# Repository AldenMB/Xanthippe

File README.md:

# Xanthippe

This is the validation back-end for my TI-30Xa emulator. It is constantly pressing buttons on a TI-30Xa calculator and recording what the LCD shows. The results get stored in an SQLite database. The database is too big to be stored on github, but you can download a CSV from [https://home.aldenbradford.com:58086/](https://home.aldenbradford.com:58086/). In addition, whenever anyone uses the calculator at [https://aldenbradford.com/calculator_emulator/](https://aldenbradford.com/calculator_emulator/) the sequence of button presses is sent to Xanthippe to be tested. It will show up in the database the following day.

For more information about this project, [please see my blog](https://aldenbradford.com/tag/xanthippe.html).

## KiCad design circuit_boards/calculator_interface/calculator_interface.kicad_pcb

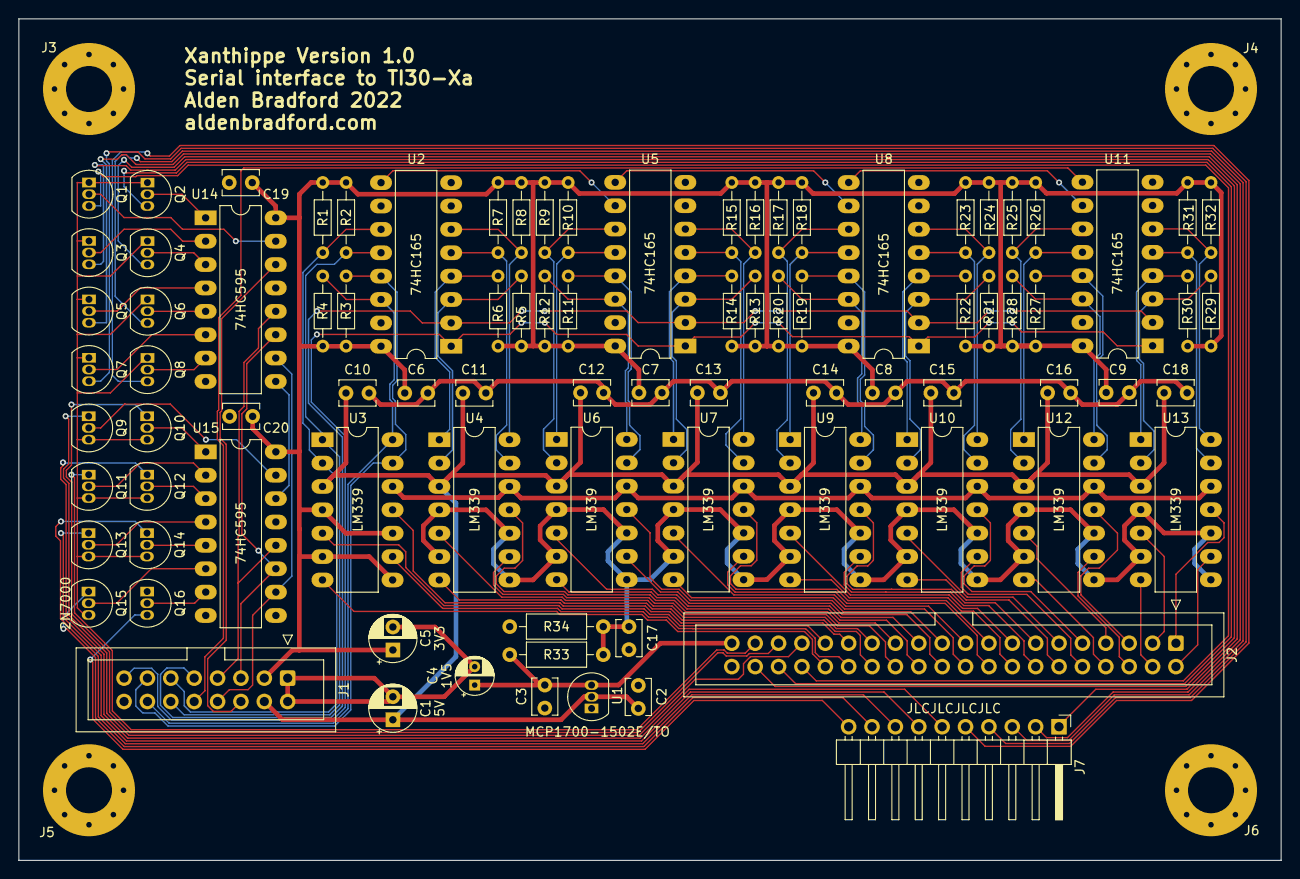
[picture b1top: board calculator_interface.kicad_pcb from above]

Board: 2 copper layers, 137.2 x 91.4 mm, 92 parts (0 on the bottom side), 113 nets.

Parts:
C1, C5: 100uF; CP_Radial_D5.0mm_P2.50mm
C2, C3, C6, C7, C8, C9, C10, C11, C12, C13, C14, C15, C16, C17, C18, C19, C20: 0.1uF; C_Disc_D3.8mm_W2.6mm_P2.50mm
C4: 10uF; CP_Radial_D4.0mm_P2.00mm
J1: Conn_02x08_Interface_Side; IDC-Header_2x08_P2.54mm_Vertical
J2: Conn_02x20_TI30XA; IDC-Header_2x20_P2.54mm_Vertical
J3, J4, J5, J6: Conn_01x01; MountingHole_5mm_Pad_Via
J7: Conn_01x10_TI30XA; PinHeader_1x10_P2.54mm_Horizontal
Q1, Q2, Q3, Q4, Q5, Q6, Q7, Q8, Q9, Q10, Q11, Q12, Q13, Q14, Q15, Q16: 2N7000; TO-92_Inline
R1, R2, R3, R4, R5, R6, R7, R8, R9, R10, R11, R12, R13, R14, R15, R16, R17, R18, R19, R20, R21, R22, R23, R24, R25, R26, R27, R28, R29, R30, R31, R32: 100K; R_Axial_DIN0204_L3.6mm_D1.6mm_P7.62mm_Horizontal
R33, R34: 100R; R_Axial_DIN0207_L6.3mm_D2.5mm_P10.16mm_Horizontal
U1: MCP1700-1502E/TO; TO-92_Inline
U2, U5, U8, U11: 74HC165; DIP-16_W7.62mm_LongPads
U3, U4, U6, U7, U9, U10, U12, U13: LM339; DIP-14_W7.62mm_LongPads
U14, U15: 74HC595; DIP-16_W7.62mm_LongPads

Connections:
+1V5: C3.1, C4.1, J2.39 (B+), R33.1, U1.3 (VOUT)
+3V3: C5.1, C6.2, C7.2, C8.2, C9.2, C19.2, C20.1, J1.3 (3V3), R1.1, R2.1, R3.1, R4.1, R5.1, R6.1, R7.1, R8.1, R9.1, R10.1, R11.1, R12.1, R13.1, R14.1, R15.1, R16.1, R17.1, R18.1, R19.1, R20.1, R21.1, R22.1, R23.1, R24.1, R25.1, R26.1, R27.1, R28.1, R29.1, R30.1, R31.1, R32.1, U2.16 (VCC), U3.4 (-), U3.6 (-), U3.8 (-), U3.10 (-), U5.16 (VCC), U8.16 (VCC), U11.16 (VCC), U14.16 (VCC), U15.16 (VCC)
+5V: C1.1, C2.1, C10.1, C11.1, C12.1, C13.1, C14.1, C15.1, C16.1, C18.1, J1.4 (5V), U1.2 (VIN), U3.3 (V+), U4.3 (V+), U6.3 (V+), U7.3 (V+), U9.3 (V+), U10.3 (V+), U12.3 (V+), U13.3 (V+)
/Keypad Driving/A0: J2.34 (A0), Q1.3 (D)
/Keypad Driving/A1: J2.36 (A1), Q2.3 (D)
/Keypad Driving/A2: J2.38 (A2), Q3.3 (D)
/Keypad Driving/A3: J7.1 (A3), Q4.3 (D)
/Keypad Driving/A4: J7.2 (A4), Q5.3 (D)
/Keypad Driving/A5: J7.3 (A5), Q6.3 (D)
/Keypad Driving/A6: J7.4 (A6), Q7.3 (D)
/Keypad Driving/A7: J7.5 (A7), Q8.3 (D)
/Keypad Driving/B0: J2.33 (B0), Q9.1 (S)
/Keypad Driving/B1: J2.35 (B1), Q10.1 (S)
/Keypad Driving/B2: J2.37 (B2), Q11.1 (S)
/Keypad Driving/B3: J7.6 (B3), Q12.1 (S)
/Keypad Driving/B4: J7.7 (B4), Q13.1 (S)
/Keypad Driving/B5: J7.8 (B5), Q14.1 (S)
/Keypad Driving/B6: J7.9 (B6), Q15.1 (S)
/Keypad Driving/CLOCK: J1.5 (KEYPAD_CLOCK), U14.11 (SRCLK), U15.11 (SRCLK)
/Keypad Driving/DATA: J1.6 (KEYPAD_DATA), U14.14 (SER)
/Keypad Driving/RESET: J7.10 (RESET), Q16.3 (D)
/Keypad Driving/SHOW: J1.7 (KEYPAD_SHOW), U14.12 (RCLK), U15.12 (RCLK)
/Keypad Driving/XA0: Q1.2 (G), U14.15 (QA)
/Keypad Driving/XA1: Q2.2 (G), U14.1 (QB)
/Keypad Driving/XA2: Q3.2 (G), U14.2 (QC)
/Keypad Driving/XA3: Q4.2 (G), U14.3 (QD)
/Keypad Driving/XA4: Q5.2 (G), U14.4 (QE)
/Keypad Driving/XA5: Q6.2 (G), U14.5 (QF)
/Keypad Driving/XA6: Q7.2 (G), U14.6 (QG)
/Keypad Driving/XA7: Q8.2 (G), U14.7 (QH)
/Keypad Driving/XB0: Q9.2 (G), U15.15 (QA)
/Keypad Driving/XB1: Q10.2 (G), U15.1 (QB)
/Keypad Driving/XB2: Q11.2 (G), U15.2 (QC)
/Keypad Driving/XB3: Q12.2 (G), U15.3 (QD)
/Keypad Driving/XB4: Q13.2 (G), U15.4 (QE)
/Keypad Driving/XB5: Q14.2 (G), U15.5 (QF)
/Keypad Driving/XB6: Q15.2 (G), U15.6 (QG)
/Keypad Driving/XRESET: Q16.2 (G), U15.7 (QH)
/Keypad Driving/~BLANK: J1.8 (KEYPAD_~BLANK), U14.10 (~SRCLR), U15.10 (~SRCLR)
/LCD Reading/CLOCK: J1.9 (LCD_CLOCK), U2.2 (CP), U5.2 (CP), U8.2 (CP), U11.2 (CP)
/LCD Reading/Comparator reference: C17.1, R33.2, R34.1, U4.4 (-), U4.6 (-), U4.8 (-), U4.10 (-), U6.4 (-), U6.6 (-), U6.8 (-), U6.10 (-), U7.4 (-), U7.6 (-), U7.8 (-), U7.10 (-), U9.4 (-), U9.6 (-), U9.8 (-), U9.10 (-), U10.4 (-), U10.6 (-), U10.8 (-), U10.10 (-), U12.4 (-), U12.6 (-), U12.8 (-), U12.10 (-), U13.4 (-), U13.6 (-), U13.8 (-), U13.10 (-)
/LCD Reading/DAT-1: J1.11 (LCD_PLANE_1), R1.2, U2.11 (D0), U3.2
/LCD Reading/DAT-2: J1.12 (LCD_PLANE_2), R2.2, U2.12 (D1), U3.1
/LCD Reading/DAT-3: J1.13 (LCD_PLANE_3), R3.2, U2.13 (D2), U3.13
/LCD Reading/DAT-4: J1.14 (LCD_PLANE_4), R4.2, U2.14 (D3), U3.14
/LCD Reading/DAT-5: R5.2, U2.3 (D4), U4.2
/LCD Reading/DAT-6: R6.2, U2.4 (D5), U4.1
/LCD Reading/DAT-7: R7.2, U2.5 (D6), U4.13
/LCD Reading/DAT-8: R8.2, U2.6 (D7), U4.14
/LCD Reading/DAT-9: R9.2, U5.11 (D0), U6.2
/LCD Reading/DAT-10: R10.2, U5.12 (D1), U6.1
/LCD Reading/DAT-11: R11.2, U5.13 (D2), U6.13
/LCD Reading/DAT-12: R12.2, U5.14 (D3), U6.14
/LCD Reading/DAT-13: R13.2, U5.3 (D4), U7.2
/LCD Reading/DAT-14: R14.2, U5.4 (D5), U7.1
/LCD Reading/DAT-15: R15.2, U5.5 (D6), U7.13
/LCD Reading/DAT-16: R16.2, U5.6 (D7), U7.14
/LCD Reading/DAT-17: R17.2, U8.11 (D0), U9.2
/LCD Reading/DAT-18: R18.2, U8.12 (D1), U9.1
/LCD Reading/DAT-19: R19.2, U8.13 (D2), U9.13
/LCD Reading/DAT-20: R20.2, U8.14 (D3), U9.14
/LCD Reading/DAT-21: R21.2, U8.3 (D4), U10.2
/LCD Reading/DAT-22: R22.2, U8.4 (D5), U10.1
/LCD Reading/DAT-23: R23.2, U8.5 (D6), U10.13
/LCD Reading/DAT-24: R24.2, U8.6 (D7), U10.14
/LCD Reading/DAT-25: R25.2, U11.11 (D0), U12.2
/LCD Reading/DAT-26: R26.2, U11.12 (D1), U12.1
/LCD Reading/DAT-27: R27.2, U11.13 (D2), U12.13
/LCD Reading/DAT-28: R28.2, U11.14 (D3), U12.14
/LCD Reading/DAT-29: R29.2, U11.3 (D4), U13.2
/LCD Reading/DAT-30: R30.2, U11.4 (D5), U13.1
/LCD Reading/DAT-31: R31.2, U11.5 (D6), U13.13
/LCD Reading/DAT-32: R32.2, U11.6 (D7), U13.14
/LCD Reading/DATA: J1.10 (LCD_DATA), U11.9 (Q7)
/LCD Reading/LCD-1: J2.31 (LCD_1(D)), U3.5 (+)
/LCD Reading/LCD-2: J2.32 (LCD_2(C)), U3.7 (+)
/LCD Reading/LCD-3: J2.29 (LCD_3(A)), U3.11 (+)
/LCD Reading/LCD-4: J2.30 (LCD_4(B)), U3.9 (+)
/LCD Reading/LCD-5: J2.27 (LCD_5), U4.5 (+)
/LCD Reading/LCD-6: J2.28 (LCD_6), U4.7 (+)
/LCD Reading/LCD-7: J2.25 (LCD_7), U4.11 (+)
/LCD Reading/LCD-8: J2.26 (LCD_8), U4.9 (+)
/LCD Reading/LCD-9: J2.23 (LCD_9), U6.5 (+)
/LCD Reading/LCD-10: J2.24 (LCD_10), U6.7 (+)
/LCD Reading/LCD-11: J2.21 (LCD_11), U6.11 (+)
/LCD Reading/LCD-12: J2.22 (LCD_12), U6.9 (+)
/LCD Reading/LCD-13: J2.19 (LCD_13), U7.5 (+)
/LCD Reading/LCD-14: J2.20 (LCD_14), U7.7 (+)
/LCD Reading/LCD-15: J2.17 (LCD_15), U7.11 (+)
/LCD Reading/LCD-16: J2.18 (LCD_16), U7.9 (+)
/LCD Reading/LCD-17: J2.15 (LCD_17), U9.5 (+)
/LCD Reading/LCD-18: J2.16 (LCD_18), U9.7 (+)
/LCD Reading/LCD-19: J2.13 (LCD_19), U9.11 (+)
/LCD Reading/LCD-20: J2.14 (LCD_20), U9.9 (+)
/LCD Reading/LCD-21: J2.11 (LCD_21), U10.5 (+)
/LCD Reading/LCD-22: J2.12 (LCD_22), U10.7 (+)
/LCD Reading/LCD-23: J2.9 (LCD_23), U10.11 (+)
/LCD Reading/LCD-24: J2.10 (LCD_24), U10.9 (+)
/LCD Reading/LCD-25: J2.7 (LCD_25), U12.5 (+)
/LCD Reading/LCD-26: J2.8 (LCD_26), U12.7 (+)
/LCD Reading/LCD-27: J2.5 (LCD_27), U12.11 (+)
/LCD Reading/LCD-28: J2.6 (LCD_28), U12.9 (+)
/LCD Reading/LCD-29: J2.3 (LCD_29), U13.5 (+)
/LCD Reading/LCD-30: J2.4 (LCD_30), U13.7 (+)
/LCD Reading/LCD-31: J2.1 (LCD_31), U13.11 (+)
/LCD Reading/LCD-32: J2.2 (LCD_32), U13.9 (+)
/LCD Reading/~SAMPLE: J1.15 (LCD_~SAMPLE), U2.1 (~PL), U5.1 (~PL), U8.1 (~PL), U11.1 (~PL)
GND: C1.2, C2.2, C3.2, C4.2, C5.2, C6.1, C7.1, C8.1, C9.1, C10.2, C11.2, C12.2, C13.2, C14.2, C15.2, C16.2, C17.2, C18.2, C19.1, C20.2, J1.1 (GND), J1.2 (GND2), J1.16 (GND3), J2.40 (GND), J3.1, J4.1, J5.1, J6.1, Q16.1 (S), R34.2, U1.1 (GND), U2.8 (GND), U2.10 (DS), U2.15 (~CE), U3.12 (V-), U4.12 (V-), U5.8 (GND), U5.15 (~CE), U6.12 (V-), U7.12 (V-), U8.8 (GND), U8.15 (~CE), U9.12 (V-), U10.12 (V-), U11.8 (GND), U11.15 (~CE), U12.12 (V-), U13.12 (V-), U14.8 (GND), U14.13 (~OE), U15.8 (GND), U15.13 (~OE)
unnamed: Q1.1 (S), Q2.1 (S), Q3.1 (S), Q4.1 (S), Q5.1 (S), Q6.1 (S), Q7.1 (S), Q8.1 (S), Q9.3 (D), Q10.3 (D), Q11.3 (D), Q12.3 (D), Q13.3 (D), Q14.3 (D), Q15.3 (D)
unnamed: U2.9 (Q7), U5.10 (DS)
unnamed: U5.9 (Q7), U8.10 (DS)
unnamed: U8.9 (Q7), U11.10 (DS)
unnamed: U14.9 (QH'), U15.14 (SER)

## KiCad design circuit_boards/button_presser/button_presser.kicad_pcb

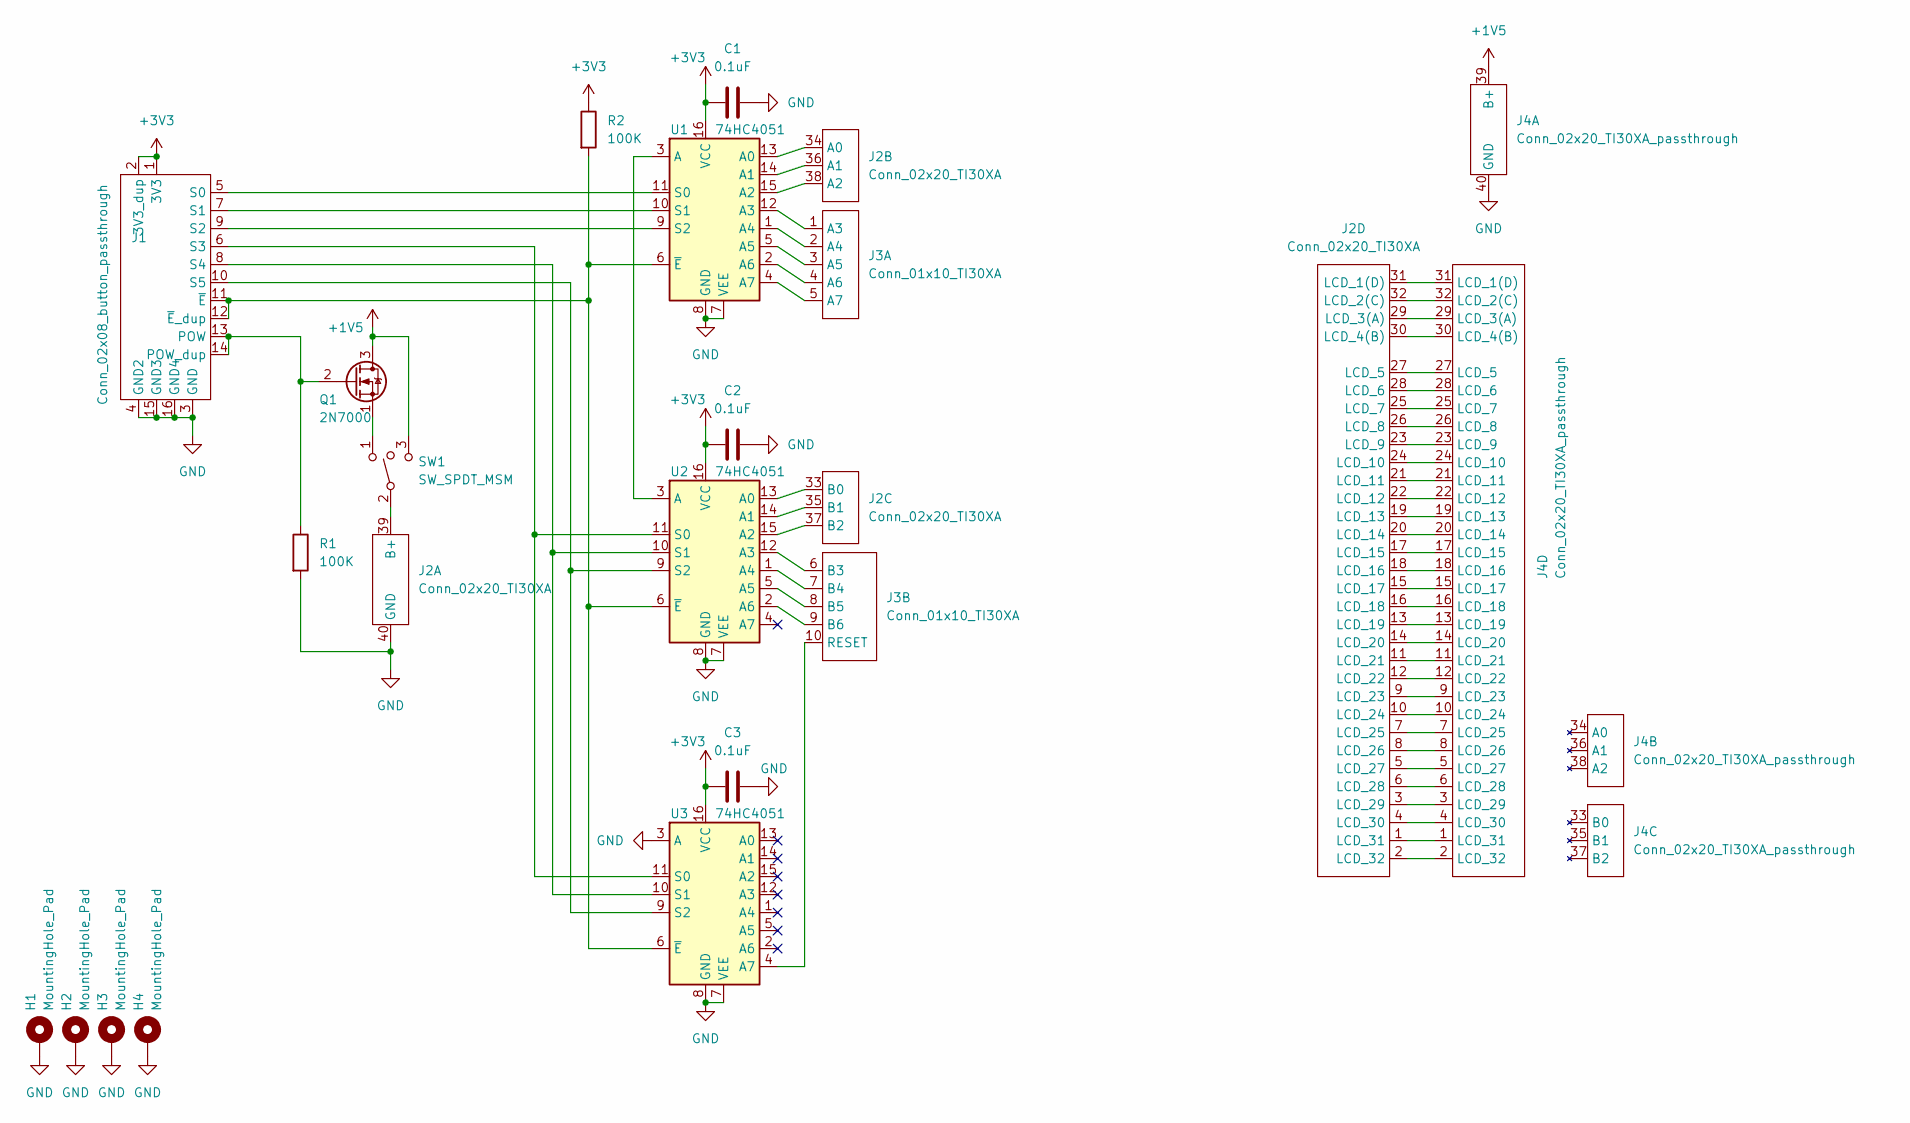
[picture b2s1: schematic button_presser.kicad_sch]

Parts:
C1, C2, C3: 0.1uF; C_Disc_D5.0mm_W2.5mm_P2.50mm
H1, H2, H3, H4: MountingHole_Pad; MountingHole_5mm_Pad_Via
J1: Conn_02x08_button_passthrough; IDC-Header_2x08_P2.54mm_Vertical
J2: Conn_02x20_TI30XA; IDC-Header_2x20_P2.54mm_Vertical
J3: Conn_01x10_TI30XA; PinHeader_1x10_P2.54mm_Horizontal
J4: Conn_02x20_TI30XA_passthrough; IDC-Header_2x20_P2.54mm_Vertical
Q1: 2N7000; TO-92_Inline_Wide
R1, R2: 100K; R_Axial_DIN0411_L9.9mm_D3.6mm_P15.24mm_Horizontal
SW1: SW_SPDT_MSM; Switch_Jumper
U1, U2, U3: 74HC4051; DIP-16_W7.62mm_LongPads

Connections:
+1V5: J4.39 (B+), Q1.3 (D), SW1.3
+3V3: C1.1, C2.1, C3.1, J1.1 (3V3), J1.2 (3V3_dup), R2.1, U1.16 (VCC), U2.16 (VCC), U3.16 (VCC)
GND: C1.2, C2.2, C3.2, H1.1, H2.1, H3.1, H4.1, J1.3 (GND), J1.4 (GND2), J1.15 (GND3), J1.16 (GND4), J2.40 (GND), J4.40 (GND), R1.2, U1.7 (VEE), U1.8 (GND), U2.7 (VEE), U2.8 (GND), U3.3 (A), U3.7 (VEE), U3.8 (GND)
unnamed: J1.5 (S0), U1.11 (S0)
unnamed: J1.6 (S3), U2.11 (S0), U3.11 (S0)
unnamed: J1.7 (S1), U1.10 (S1)
unnamed: J1.8 (S4), U2.10 (S1), U3.10 (S1)
unnamed: J1.9 (S2), U1.9 (S2)
unnamed: J1.10 (S5), U2.9 (S2), U3.9 (S2)
unnamed: J1.11 (~E), J1.12 (~E_dup), R2.2, U1.6 (~E), U2.6 (~E), U3.6 (~E)
unnamed: J1.13 (POW), J1.14 (POW_dup), Q1.2 (G), R1.1
unnamed: J2.1 (LCD_31), J4.1 (LCD_31)
unnamed: J2.2 (LCD_32), J4.2 (LCD_32)
unnamed: J2.3 (LCD_29), J4.3 (LCD_29)
unnamed: J2.4 (LCD_30), J4.4 (LCD_30)
unnamed: J2.5 (LCD_27), J4.5 (LCD_27)
unnamed: J2.6 (LCD_28), J4.6 (LCD_28)
unnamed: J2.7 (LCD_25), J4.7 (LCD_25)
unnamed: J2.8 (LCD_26), J4.8 (LCD_26)
unnamed: J2.9 (LCD_23), J4.9 (LCD_23)
unnamed: J2.10 (LCD_24), J4.10 (LCD_24)
unnamed: J2.11 (LCD_21), J4.11 (LCD_21)
unnamed: J2.12 (LCD_22), J4.12 (LCD_22)
unnamed: J2.13 (LCD_19), J4.13 (LCD_19)
unnamed: J2.14 (LCD_20), J4.14 (LCD_20)
unnamed: J2.15 (LCD_17), J4.15 (LCD_17)
unnamed: J2.16 (LCD_18), J4.16 (LCD_18)
unnamed: J2.17 (LCD_15), J4.17 (LCD_15)
unnamed: J2.18 (LCD_16), J4.18 (LCD_16)
unnamed: J2.19 (LCD_13), J4.19 (LCD_13)
unnamed: J2.20 (LCD_14), J4.20 (LCD_14)
unnamed: J2.21 (LCD_11), J4.21 (LCD_11)
unnamed: J2.22 (LCD_12), J4.22 (LCD_12)
unnamed: J2.23 (LCD_9), J4.23 (LCD_9)
unnamed: J2.24 (LCD_10), J4.24 (LCD_10)
unnamed: J2.25 (LCD_7), J4.25 (LCD_7)
unnamed: J2.26 (LCD_8), J4.26 (LCD_8)
unnamed: J2.27 (LCD_5), J4.27 (LCD_5)
unnamed: J2.28 (LCD_6), J4.28 (LCD_6)
unnamed: J2.29 (LCD_3(A)), J4.29 (LCD_3(A))
unnamed: J2.30 (LCD_4(B)), J4.30 (LCD_4(B))
unnamed: J2.31 (LCD_1(D)), J4.31 (LCD_1(D))
unnamed: J2.32 (LCD_2(C)), J4.32 (LCD_2(C))
unnamed: J2.33 (B0), U2.13 (A0)
unnamed: J2.34 (A0), U1.13 (A0)
unnamed: J2.35 (B1), U2.14 (A1)
unnamed: J2.36 (A1), U1.14 (A1)
unnamed: J2.37 (B2), U2.15 (A2)
unnamed: J2.38 (A2), U1.15 (A2)
unnamed: J2.39 (B+), SW1.2
unnamed: J3.1 (A3), U1.12 (A3)
unnamed: J3.2 (A4), U1.1 (A4)
unnamed: J3.3 (A5), U1.5 (A5)
unnamed: J3.4 (A6), U1.2 (A6)
unnamed: J3.5 (A7), U1.4 (A7)
unnamed: J3.6 (B3), U2.12 (A3)
unnamed: J3.7 (B4), U2.1 (A4)
unnamed: J3.8 (B5), U2.5 (A5)
unnamed: J3.9 (B6), U2.2 (A6)
unnamed: J3.10 (RESET), U3.4 (A7)
unnamed: Q1.1 (S), SW1.1
unnamed: U1.3 (A), U2.3 (A)

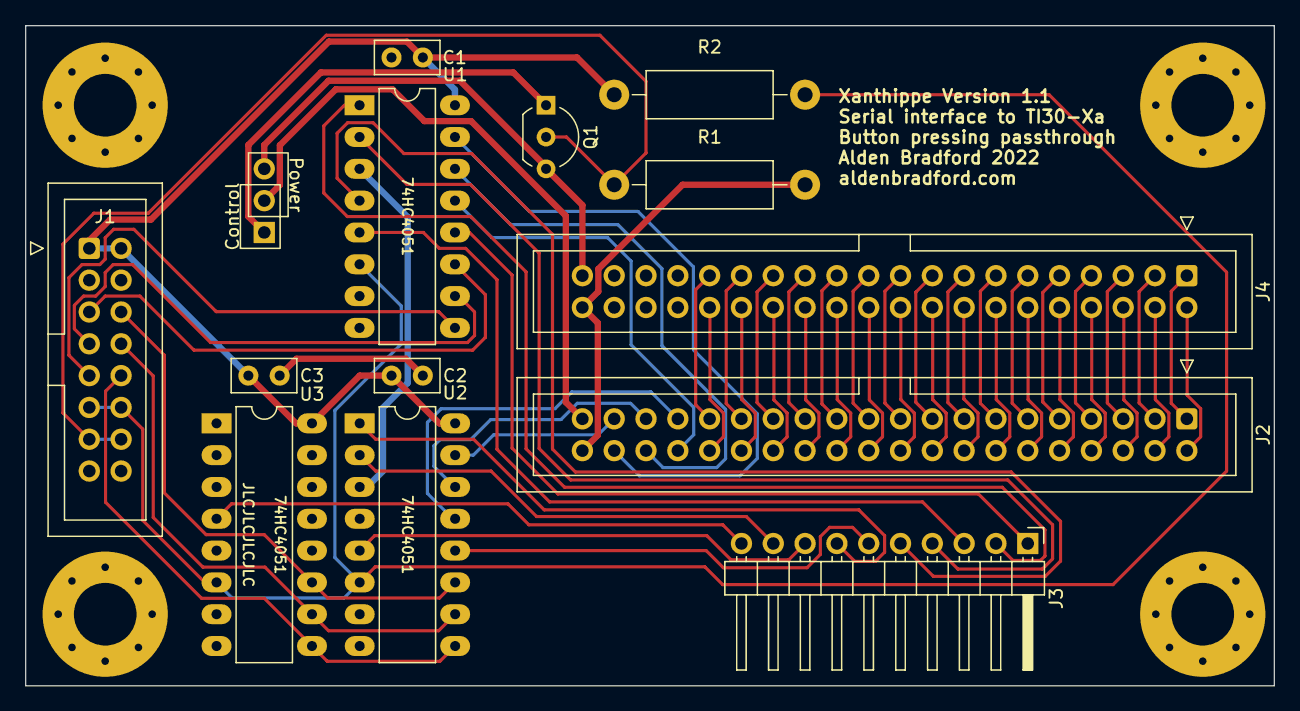
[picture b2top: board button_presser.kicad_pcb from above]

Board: 2 copper layers, 99.7 x 52.7 mm, 18 parts (0 on the bottom side), 62 nets.

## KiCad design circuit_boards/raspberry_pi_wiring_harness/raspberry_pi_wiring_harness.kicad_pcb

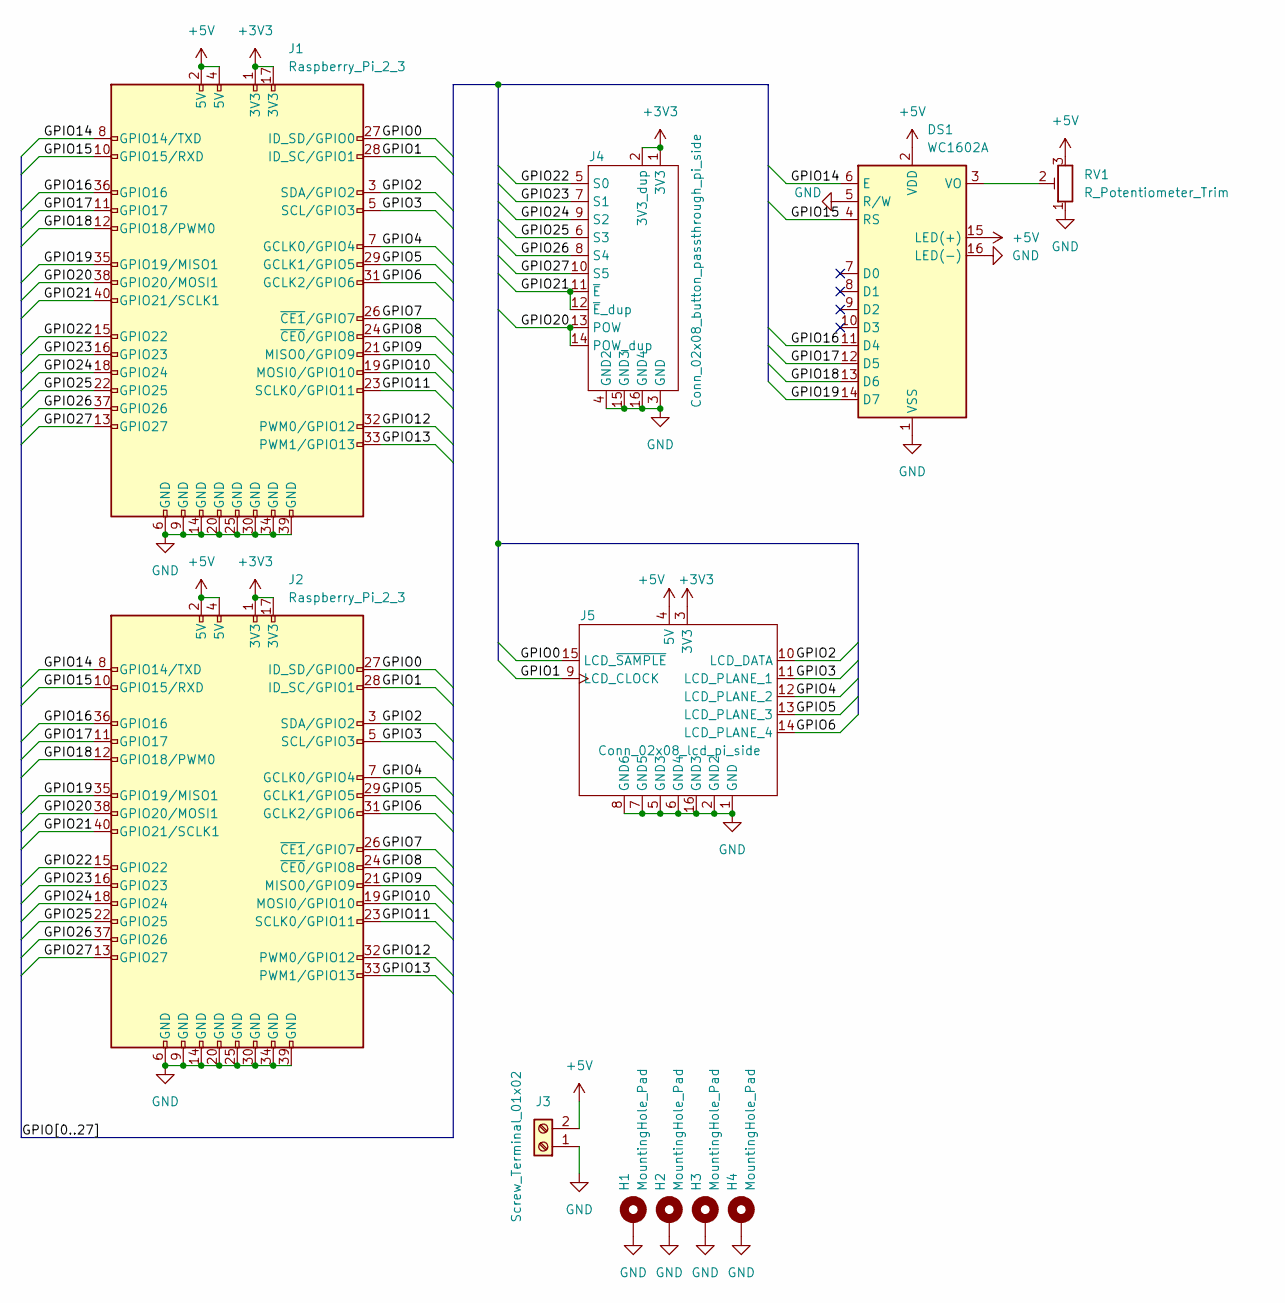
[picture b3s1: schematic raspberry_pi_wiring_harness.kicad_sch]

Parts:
DS1: WC1602A
H1, H2, H3, H4: MountingHole_Pad; MountingHole_5mm_Pad_Via
J1, J2: Raspberry_Pi_2_3; IDC-Header_2x20_P2.54mm_Vertical
J3: Screw_Terminal_01x02; TerminalBlock_bornier-2_P5.08mm
J4: Conn_02x08_button_passthrough_pi_side; IDC-Header_2x08_P2.54mm_Vertical
J5: Conn_02x08_lcd_pi_side; IDC-Header_2x08_P2.54mm_Vertical
RV1: R_Potentiometer_Trim; Potentiometer_Bourns_3296W_Vertical

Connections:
+3V3: J1.1 (3V3), J1.17 (3V3), J2.1 (3V3), J2.17 (3V3), J4.1 (3V3), J4.2 (3V3_dup), J5.3 (3V3)
+5V: DS1.2 (VDD), DS1.15 (LED(+)), J1.2 (5V), J1.4 (5V), J2.2 (5V), J2.4 (5V), J3.2, J5.4 (5V), RV1.3
/GPIO0: J1.27 (ID_SD/GPIO0), J2.27 (ID_SD/GPIO0), J5.15 (LCD_~SAMPLE)
/GPIO1: J1.28 (ID_SC/GPIO1), J2.28 (ID_SC/GPIO1), J5.9 (LCD_CLOCK)
/GPIO2: J1.3 (SDA/GPIO2), J2.3 (SDA/GPIO2), J5.10 (LCD_DATA)
/GPIO3: J1.5 (SCL/GPIO3), J2.5 (SCL/GPIO3), J5.11 (LCD_PLANE_1)
/GPIO4: J1.7 (GCLK0/GPIO4), J2.7 (GCLK0/GPIO4), J5.12 (LCD_PLANE_2)
/GPIO5: J1.29 (GCLK1/GPIO5), J2.29 (GCLK1/GPIO5), J5.13 (LCD_PLANE_3)
/GPIO6: J1.31 (GCLK2/GPIO6), J2.31 (GCLK2/GPIO6), J5.14 (LCD_PLANE_4)
/GPIO7: J1.26 (~CE1/GPIO7), J2.26 (~CE1/GPIO7)
/GPIO8: J1.24 (~CE0/GPIO8), J2.24 (~CE0/GPIO8)
/GPIO9: J1.21 (MISO0/GPIO9), J2.21 (MISO0/GPIO9)
/GPIO10: J1.19 (MOSI0/GPIO10), J2.19 (MOSI0/GPIO10)
/GPIO11: J1.23 (SCLK0/GPIO11), J2.23 (SCLK0/GPIO11)
/GPIO12: J1.32 (PWM0/GPIO12), J2.32 (PWM0/GPIO12)
/GPIO13: J1.33 (PWM1/GPIO13), J2.33 (PWM1/GPIO13)
/GPIO14: DS1.6 (E), J1.8 (GPIO14/TXD), J2.8 (GPIO14/TXD)
/GPIO15: DS1.4 (RS), J1.10 (GPIO15/RXD), J2.10 (GPIO15/RXD)
/GPIO16: DS1.11 (D4), J1.36 (GPIO16), J2.36 (GPIO16)
/GPIO17: DS1.12 (D5), J1.11 (GPIO17), J2.11 (GPIO17)
/GPIO18: DS1.13 (D6), J1.12 (GPIO18/PWM0), J2.12 (GPIO18/PWM0)
/GPIO19: DS1.14 (D7), J1.35 (GPIO19/MISO1), J2.35 (GPIO19/MISO1)
/GPIO20: J1.38 (GPIO20/MOSI1), J2.38 (GPIO20/MOSI1), J4.13 (POW), J4.14 (POW_dup)
/GPIO21: J1.40 (GPIO21/SCLK1), J2.40 (GPIO21/SCLK1), J4.11 (~E), J4.12 (~E_dup)
/GPIO22: J1.15 (GPIO22), J2.15 (GPIO22), J4.5 (S0)
/GPIO23: J1.16 (GPIO23), J2.16 (GPIO23), J4.7 (S1)
/GPIO24: J1.18 (GPIO24), J2.18 (GPIO24), J4.9 (S2)
/GPIO25: J1.22 (GPIO25), J2.22 (GPIO25), J4.6 (S3)
/GPIO26: J1.37 (GPIO26), J2.37 (GPIO26), J4.8 (S4)
/GPIO27: J1.13 (GPIO27), J2.13 (GPIO27), J4.10 (S5)
GND: DS1.1 (VSS), DS1.5 (R/W), DS1.16 (LED(-)), H1.1, H2.1, H3.1, H4.1, J1.6 (GND), J1.9 (GND), J1.14 (GND), J1.20 (GND), J1.25 (GND), J1.30 (GND), J1.34 (GND), J1.39 (GND), J2.6 (GND), J2.9 (GND), J2.14 (GND), J2.20 (GND), J2.25 (GND), J2.30 (GND), J2.34 (GND), J2.39 (GND), J3.1, J4.3 (GND), J4.4 (GND2), J4.15 (GND3), J4.16 (GND4), J5.1 (GND), J5.2 (GND2), J5.5 (GND3), J5.6 (GND4), J5.7 (GND5), J5.8 (GND6), J5.16 (GND3), RV1.1
unnamed: DS1.3 (VO), RV1.2

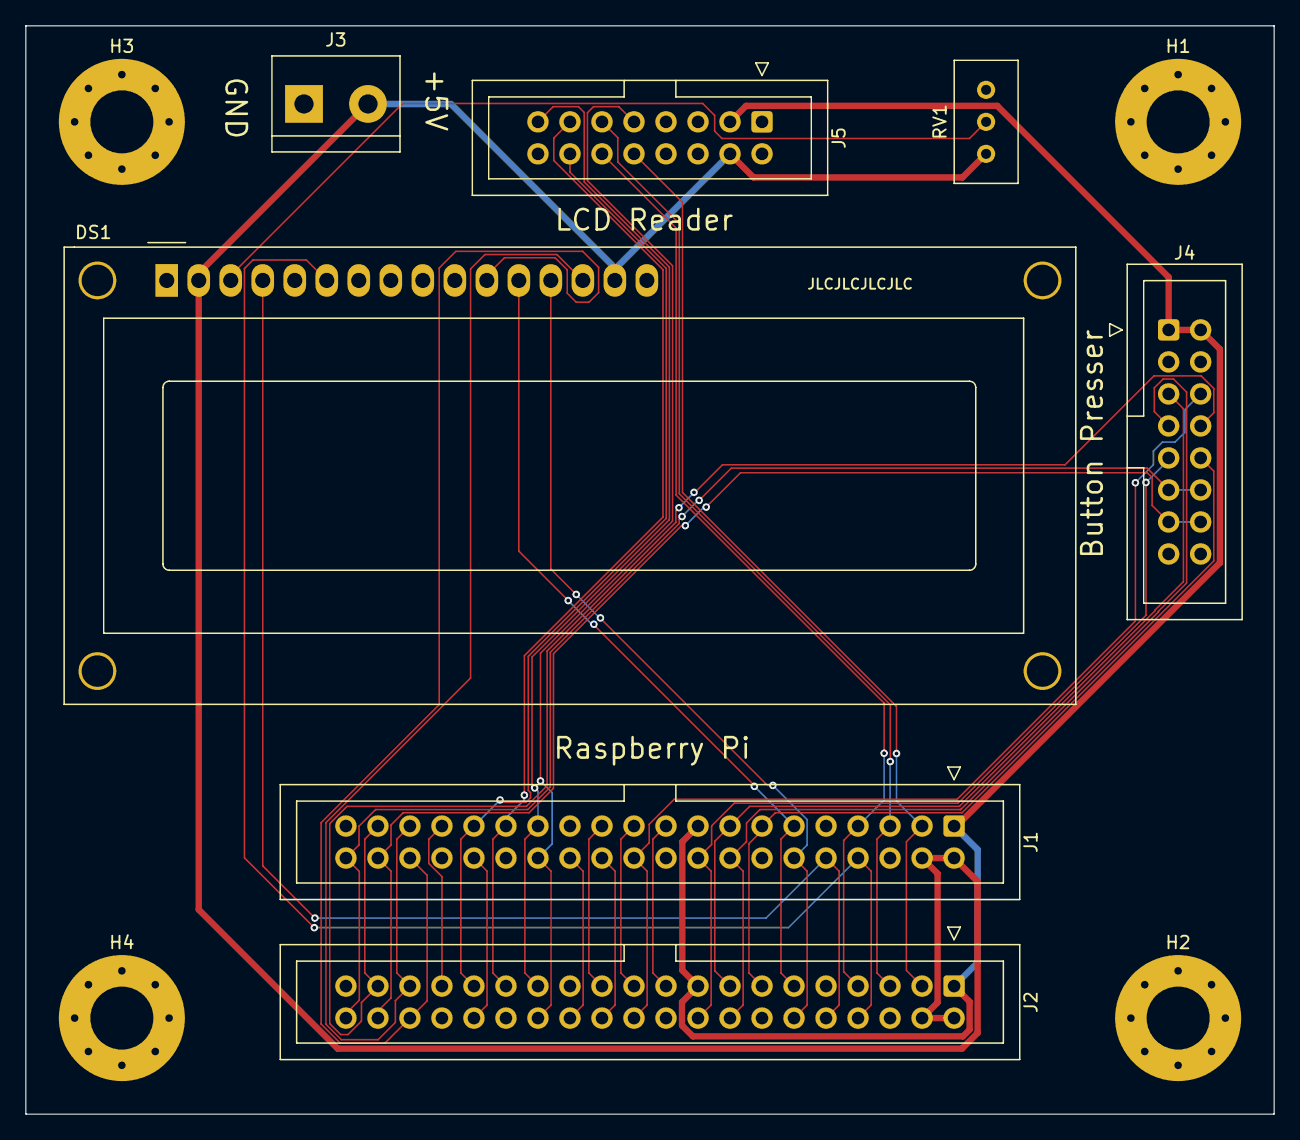
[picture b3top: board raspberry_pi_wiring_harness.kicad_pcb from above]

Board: 2 copper layers, 99.1 x 86.4 mm, 11 parts (0 on the bottom side), 32 nets.

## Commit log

2022-07-22 first draft of arduino code
2022-07-31 driver for lcd shift registers
2022-07-31 pcb for calculator interface
2022-07-31 add mounting holes
2022-07-31 remove redundant file
2022-07-31 draft ready for final review
2022-08-01 rewrite based on chip timing
2022-08-01 remove reference to global enumerate
2022-08-01 put it back as an enumerate
2022-08-01 remove flipped version
2022-08-02 changed reference voltage circuit to be compatible with voltage regulator
2022-12-22 all wired up
2022-12-22 sort pico code
2022-12-25 driver for lcd display
2022-12-25 better comments
2022-12-25 initial calculator drivers
2022-12-25 code to read shift register fast (untested)
2022-12-25 reorganize
2023-01-19 compile flags for c code
2023-01-19 fix logic errors in acquiry code
2023-01-19 testing code added to main
2023-01-19 speed up button presses
2023-01-19 compact encoding for readings
2023-01-20 log only changes
2023-01-20 tidying, better printing
2023-01-20 package up driver code
2023-01-20 interactive calculator mode
2023-01-20 prettier formatting during interactive
2023-01-21 session interface
2023-01-21 remove obsolete code
2023-01-21 automatic exploration
2023-01-21 include logging
2023-01-21 run forever
2023-01-21 hear requests
2023-01-21 use gunicorn for deployment
2023-01-21 remove windows line ending
2023-01-21 move startup script outside of repo
2023-01-22 explore requested presses
2023-01-23 save backups at regular intervals
2023-01-23 serve the database as a csv
2023-01-23 do not track the database in git
2023-01-23 remove double press
2023-01-26 increase wait time after press
2023-01-26 utility for removing a measurement from records
2023-01-26 button names should align with emulator
2023-01-26 typo
2023-01-26 more verbose
2023-01-26 sort the records by length
2023-01-27 make the calculator more patient
2023-01-31 include animation in readme
2023-02-01 be more patient to ensure display has updated
2023-02-03 prefer shorter sessions
2023-02-03 make sure reset is done correctly at the start of a session
2023-02-03 power off the calculator between sessions
2023-03-03 increase timeouts for database access
2023-03-03 extended timeout
